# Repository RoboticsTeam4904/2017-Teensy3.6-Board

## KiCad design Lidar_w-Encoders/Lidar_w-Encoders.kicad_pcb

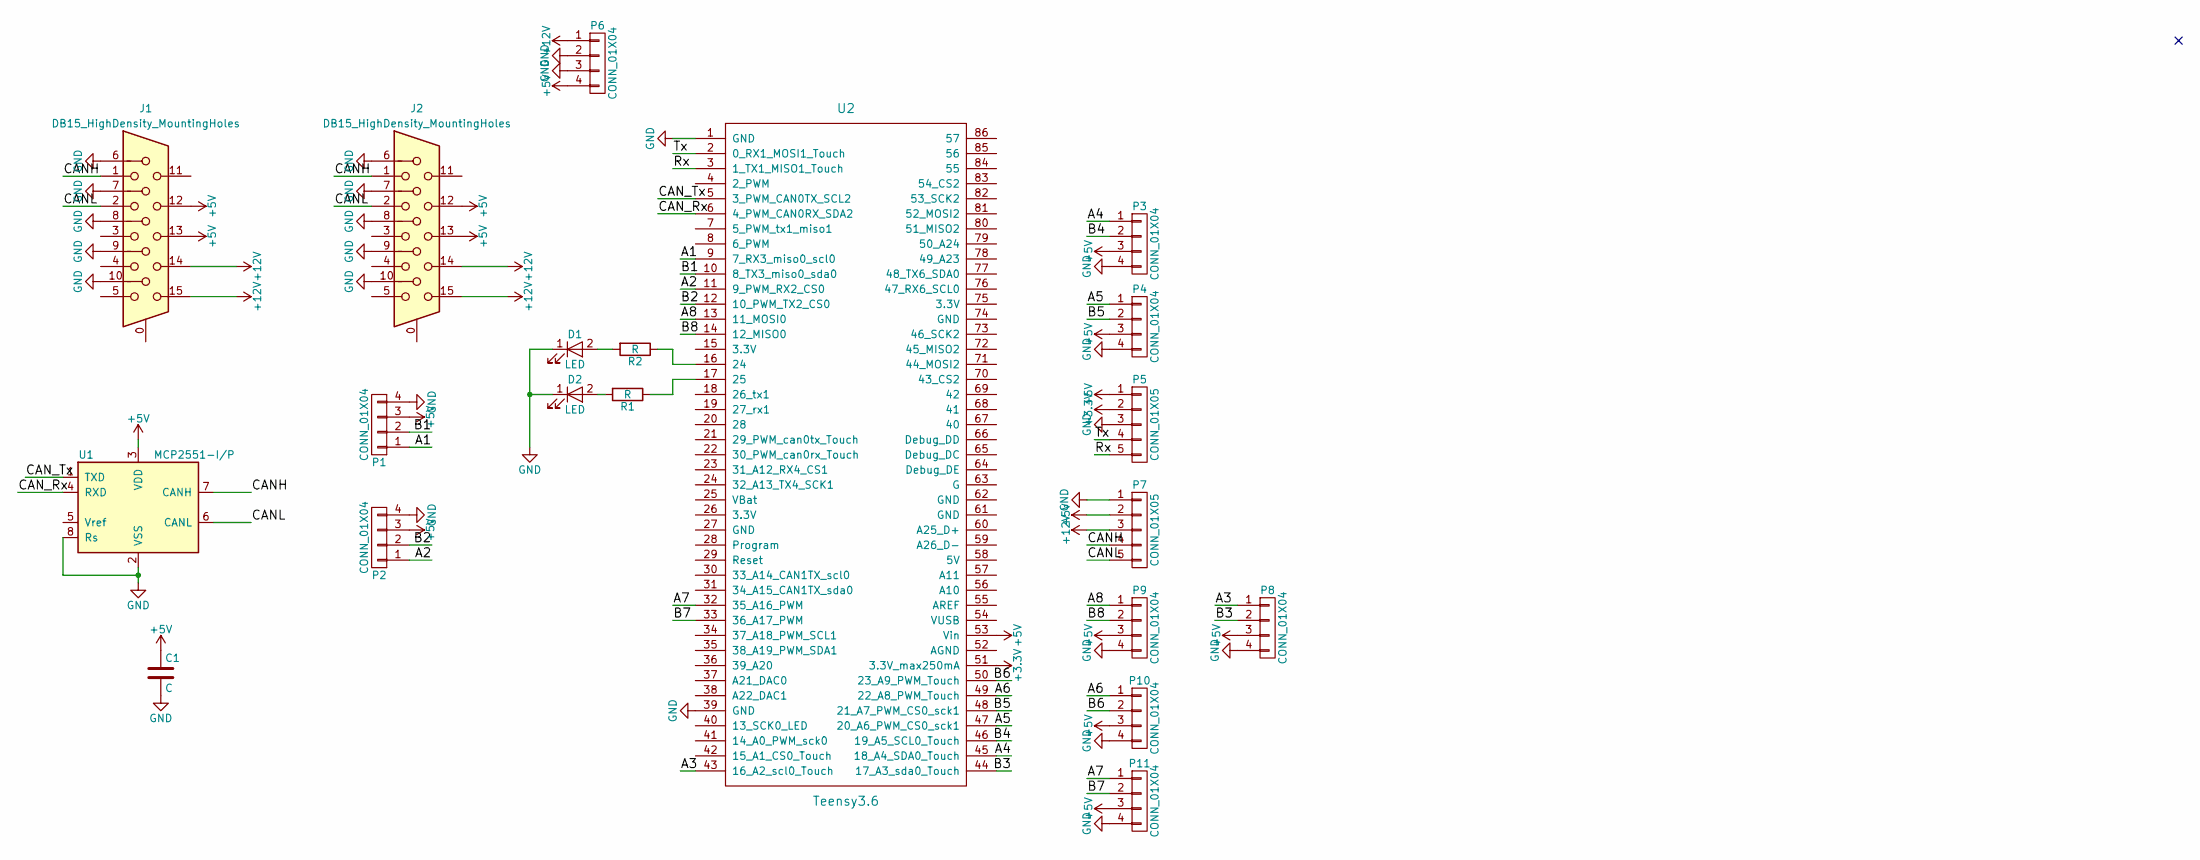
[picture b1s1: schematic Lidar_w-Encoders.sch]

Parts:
C1: C; C_Disc_D5.0mm_W2.5mm_P5.00mm
D1, D2: LED; LED-5MM
J1, J2: DB15_HighDensity_MountingHoles; conn_SPC15430
P1, P2, P3, P4, P6, P8, P9, P10, P11: CONN_01X04; Socket_Strip_Straight_1x04_Pitch2.54mm
P5: CONN_01X05; Socket_Strip_Straight_1x05_Pitch2.54mm
P7: CONN_01X05; TerminalBlock_Pheonix_PT-3.5mm_5pol
R1, R2: R; R_Box_L13.0mm_W4.0mm_P9.00mm
U1: MCP2551-I/P; DIP-8_W7.62mm_BiggerHoles
U2: Teensy3.6; Teensy35_36_LessPins

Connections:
+3V3: P5.2, U2.51 (3.3V_max250mA)
+5V: C1.1, J1.12, J1.13, J2.12, J2.13, P1.3, P2.3, P3.3, P4.3, P5.1, P6.4, P7.2, P8.3, P9.3, P10.3, P11.3, U1.3 (VDD), U2.53 (Vin)
+12V: J1.14, J1.15, J2.14, J2.15, P6.1, P7.3
/A1: P1.1, U2.9 (7_RX3_miso0_scl0)
/A2: P2.1, U2.11 (9_PWM_RX2_CS0)
/A3: P8.1, U2.43 (16_A2_scl0_Touch)
/A4: P3.1, U2.45 (18_A4_SDA0_Touch)
/A5: P4.1, U2.47 (20_A6_PWM_CS0_sck1)
/A6: P10.1, U2.49 (22_A8_PWM_Touch)
/A7: P11.1, U2.32 (35_A16_PWM)
/A8: P9.1, U2.13 (11_MOSI0)
/B1: P1.2, U2.10 (8_TX3_miso0_sda0)
/B2: P2.2, U2.12 (10_PWM_TX2_CS0)
/B3: P8.2, U2.44 (17_A3_sda0_Touch)
/B4: P3.2, U2.46 (19_A5_SCL0_Touch)
/B5: P4.2, U2.48 (21_A7_PWM_CS0_sck1)
/B6: P10.2, U2.50 (23_A9_PWM_Touch)
/B7: P11.2, U2.33 (36_A17_PWM)
/B8: P9.2, U2.14 (12_MISO0)
/CANH: J1.1, J2.1, P7.4, U1.7 (CANH)
/CANL: J1.2, J2.2, P7.5, U1.6 (CANL)
/CAN_Rx: U1.4 (RXD), U2.6 (4_PWM_CAN0RX_SDA2)
/CAN_Tx: U1.1 (TXD), U2.5 (3_PWM_CAN0TX_SCL2)
/Rx: P5.5, U2.3 (1_TX1_MISO1_Touch)
/Tx: P5.4, U2.2 (0_RX1_MOSI1_Touch)
GND: C1.2, D1.1 (K), D2.1 (K), J1.6, J1.7, J1.8, J1.9, J1.10, J2.6, J2.7, J2.8, J2.9, J2.10, P1.4, P2.4, P3.4, P4.4, P5.3, P6.2, P6.3, P7.1, P8.4, P9.4, P10.4, P11.4, U1.2 (VSS), U1.8 (Rs), U2.1 (GND), U2.39 (GND)
unnamed: D1.2 (A), R2.2
unnamed: D2.2 (A), R1.2
unnamed: R1.1, U2.17 (25)
unnamed: R2.1, U2.16 (24)

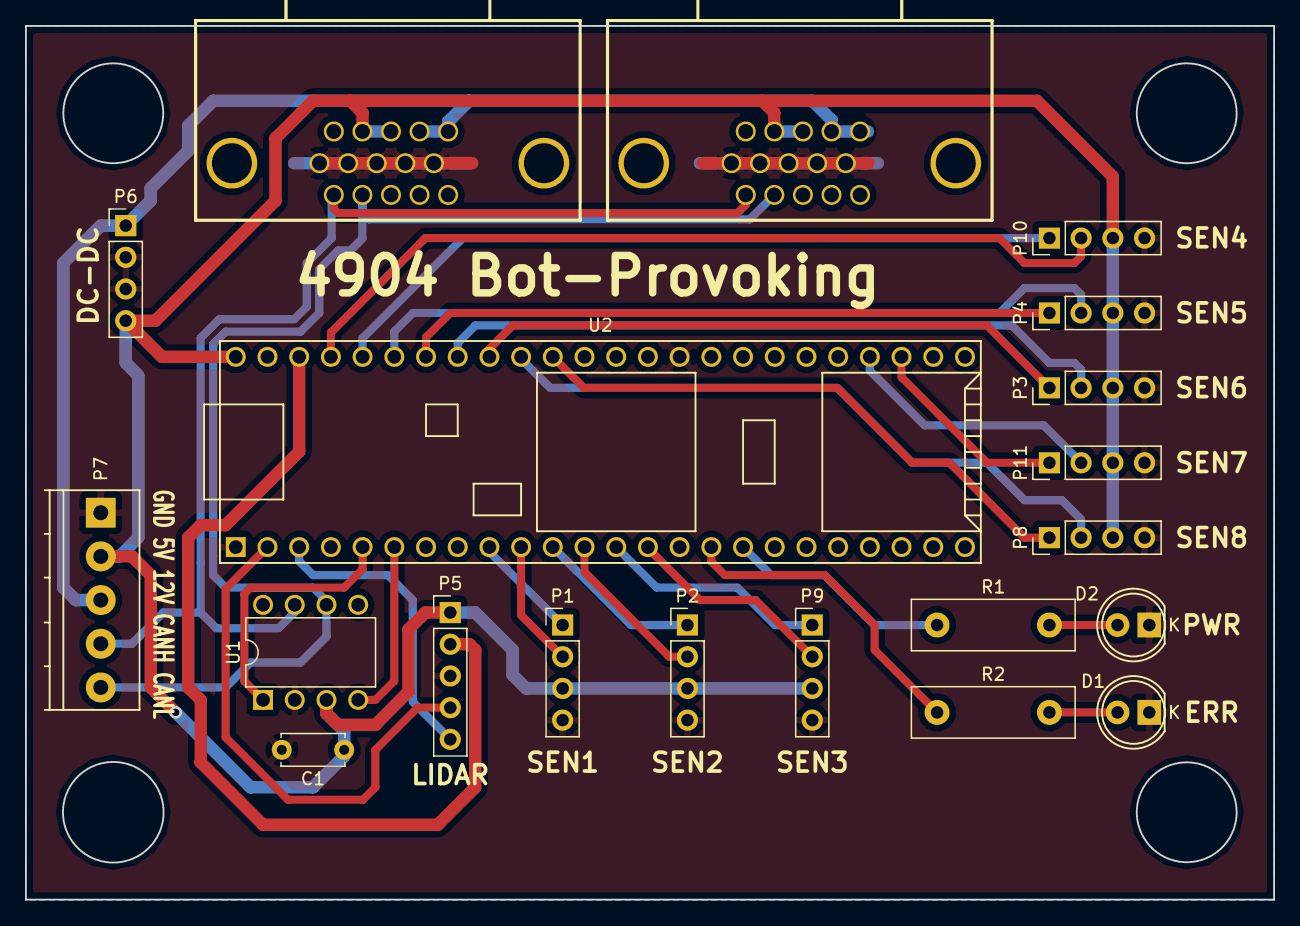
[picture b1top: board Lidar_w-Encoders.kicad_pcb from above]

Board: 2 copper layers, 100.0 x 70.0 mm, 20 parts (0 on the bottom side), 30 nets.

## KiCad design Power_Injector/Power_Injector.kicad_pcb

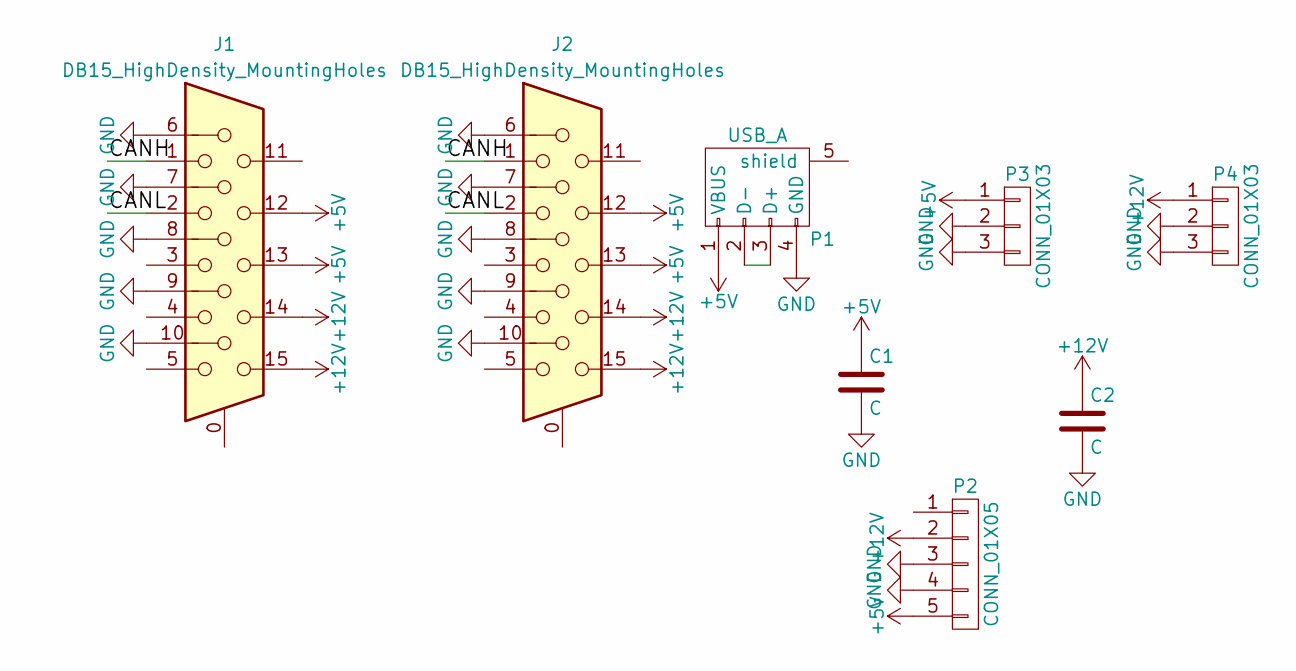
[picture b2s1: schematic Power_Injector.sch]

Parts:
C1, C2: C; C_Disc_D7.5mm_W5.0mm_P5.00mm
J1, J2: DB15_HighDensity_MountingHoles; conn_SPC15430
P1: USB_A
P2: CONN_01X05; Socket_Strip_Straight_1x05
P3, P4: CONN_01X03; TerminalBlock_Pheonix_PT-3.5mm_3pol

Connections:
+5V: C1.1, J1.12, J1.13, J2.12, J2.13, P1.1 (VBUS), P2.5, P3.1
+12V: C2.1, J1.14, J1.15, J2.14, J2.15, P2.2, P4.1
/CANH: J1.1, J2.1
/CANL: J1.2, J2.2
GND: C1.2, C2.2, J1.6, J1.7, J1.8, J1.9, J1.10, J2.6, J2.7, J2.8, J2.9, J2.10, P1.4 (GND), P2.3, P2.4, P3.2, P3.3, P4.2, P4.3
unnamed: P1.2 (D-), P1.3 (D+)

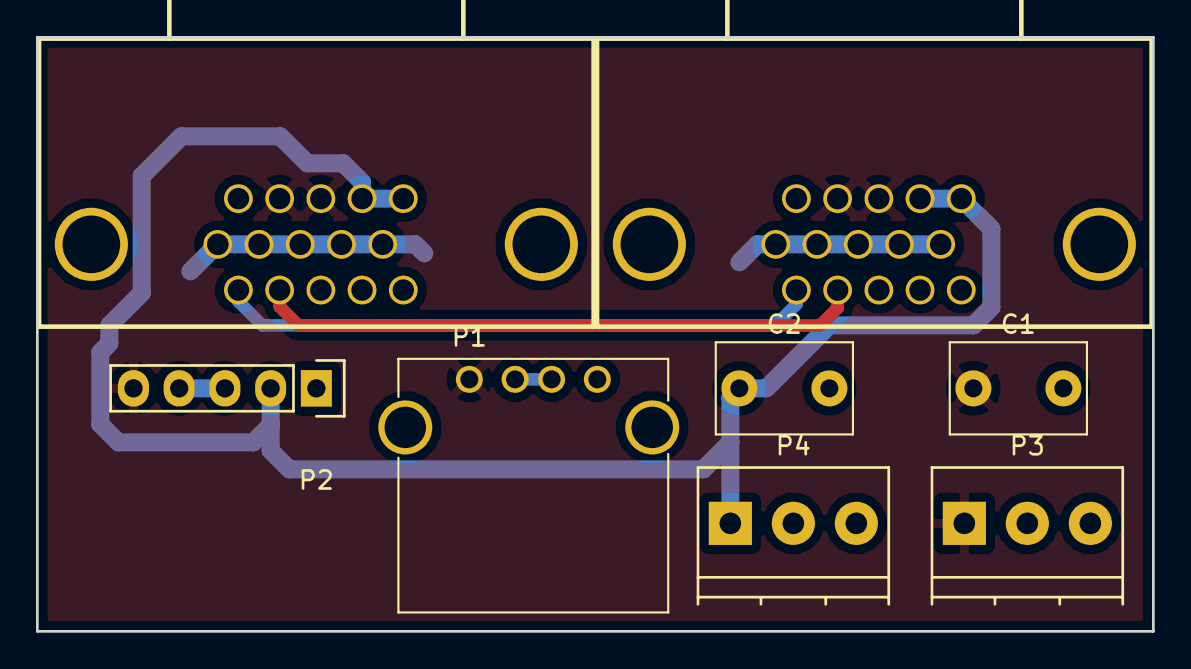
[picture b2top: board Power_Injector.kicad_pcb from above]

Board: 2 copper layers, 62.0 x 33.0 mm, 8 parts (0 on the bottom side), 6 nets.

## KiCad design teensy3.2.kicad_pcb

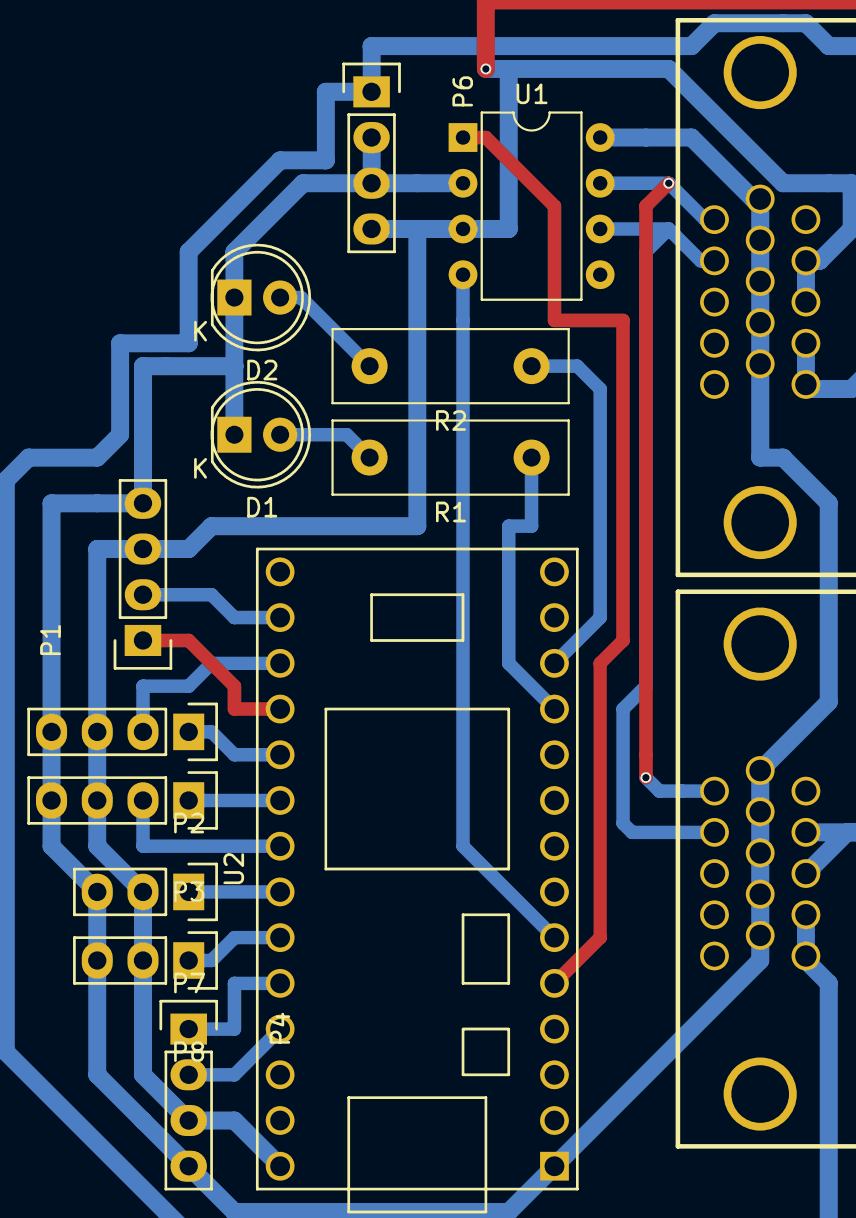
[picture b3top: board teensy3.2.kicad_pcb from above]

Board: 2 copper layers, 15 parts (0 on the bottom side), 21 nets.

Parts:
D1, D2: LED; LED-5MM
J1, J2: DB15_HighDensity_MountingHoles; conn_SPC15430
P1, P2, P3, P4, P6: CONN_01X04; Socket_Strip_Straight_1x04
P7, P8: CONN_01X03; Socket_Strip_Straight_1x03
R1, R2: R; R_Box_L13.0mm_W4.0mm_P9.00mm
U1: MCP2551-I/P; DIP-8_W7.62mm
U2: Teensy3.2; Teensy30_31_32_LC_LessPins

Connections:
+5V: J1.12, J1.13, J2.12, J2.13, P1.3, P2.3, P3.3, P4.3, P6.4, P7.2, P8.2, U1.3, U2.33
+12V: J1.14, J1.15, J2.14, J2.15, P6.1
/A1: P1.2, U2.21
/A2: P2.2, U2.22
/A3: P3.1, U2.25
/A4: P4.1, U2.29
/A7: P7.1, U2.27
/A8: P8.1, U2.28
/B1: P1.1, U2.23
/B2: P2.1, U2.24
/B3: P3.2, U2.26
/B4: P4.2, U2.30
/CAN_HIGH: J1.1, J2.1, U1.7
/CAN_LOW: J1.2, J2.2, U1.6
GND: D1.1, D2.1, J1.6, J1.7, J1.8, J1.9, J1.10, J2.6, J2.7, J2.8, J2.9, J2.10, P1.4, P2.4, P3.4, P4.4, P6.2, P6.3, P7.3, P8.3, U1.2, U1.8, U2.1
unnamed: D1.2, R1.2
unnamed: D2.2, R2.2
unnamed: R1.1, U2.11
unnamed: R2.1, U2.12
unnamed: U1.1, U2.5
unnamed: U1.4, U2.6

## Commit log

2017-01-30 Added Gitignore
2017-01-30 increased fill clearance
2017-02-05 Added Gerbers File and Ultrasonic Controller
2017-02-05 Took out VIAs; fixed fills.
2017-02-05 Reorganized. Added Power Injector Board.
2017-02-05 added extra grounds
2017-02-09 Added Ultrasonic Final and Reorganized
2017-03-14 Added 4 pin connectors and mounting holes.
2017-03-14 Added mounting holes and 4 pin connectors
2017-03-20 added connector labels and cleaned up
